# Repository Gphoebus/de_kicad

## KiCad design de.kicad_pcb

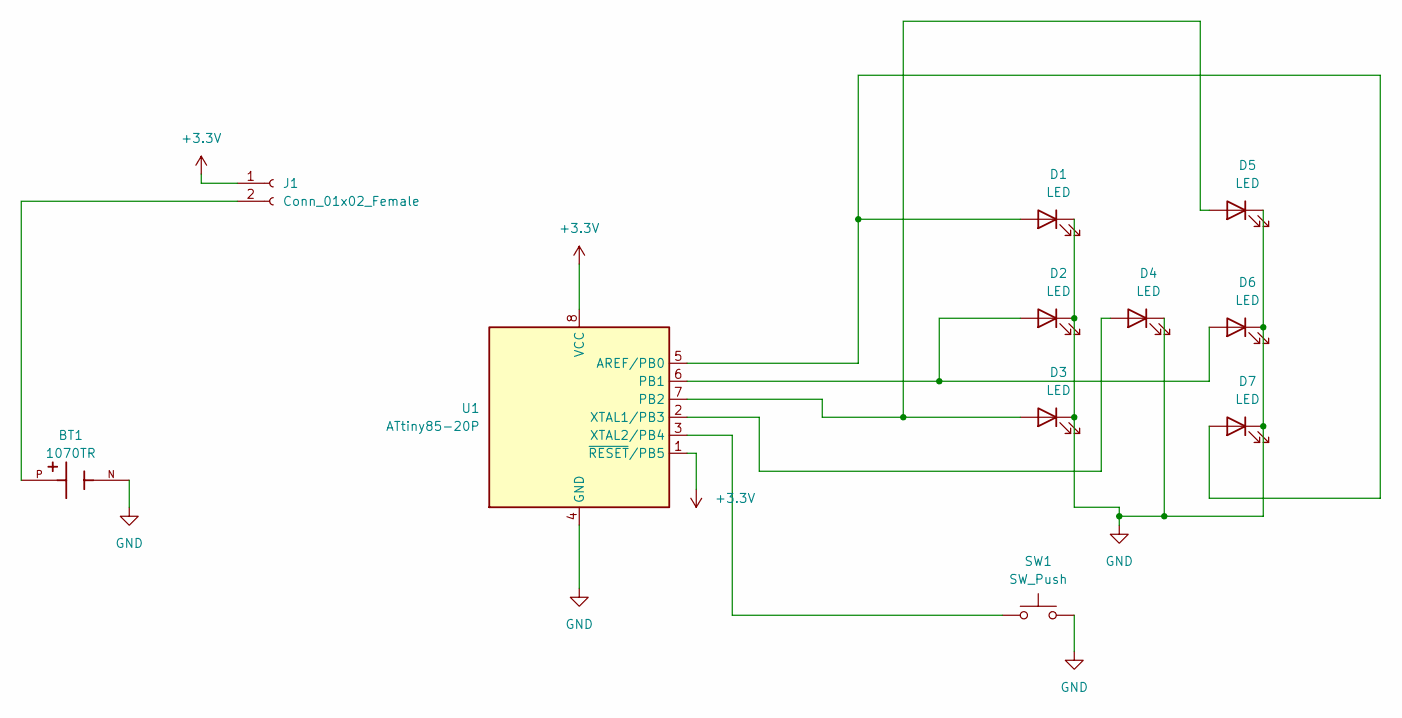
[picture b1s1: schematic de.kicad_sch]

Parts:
BT1: 1070TR; KEYSTONE_1070TR; PARTREV C
D1, D2, D3, D4, D5, D6, D7: LED; LED_D5.0mm
J1: Conn_01x02_Female; Molex_KK-254_AE-6410-02A_1x02_P2.54mm_Vertical
SW1: SW_Push; LED_D5.0mm
U1: ATtiny85-20P; DIP-8_W7.62mm

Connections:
+3V3: J1.1, U1.1 (~RESET/PB5), U1.8 (VCC)
GND: BT1.N, D1.1 (K), D2.1 (K), D3.1 (K), D4.1 (K), D5.1 (K), D6.1 (K), D7.1 (K), SW1.2, U1.4 (GND)
unnamed: D1.2 (A), D7.2 (A), U1.5 (AREF/PB0)
unnamed: D2.2 (A), D6.2 (A), U1.6 (PB1)
unnamed: D3.2 (A), D5.2 (A), U1.7 (PB2)
unnamed: D4.2 (A), U1.2 (XTAL1/PB3)
unnamed: BT1.P, J1.2
unnamed: SW1.1, U1.3 (XTAL2/PB4)

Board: 2 copper layers, 11 parts (2 on the bottom side), 8 nets, no tracks yet.
